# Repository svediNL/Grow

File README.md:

# Grow
This project uses a `Python` program in combination with an `Arduino Mega` to monitor and control factors that are involved with plant growth.

It is supposed to be used as an open-source, modular platform for growers that want to find (or create) optimal growing conditions for the growth of their plants.

The main program is started by running `python gui.py`. 
Through GUI:
- User can choose to enable/diable light as well as control intensity 
    - Manual control
    - Automatic configurable day/night cycle
- Pump is controlled with a PWM setpoint (0-255) and has external enable/disable button. 
    - The pump is interlocked (meaning it will stop) when the float switch is open, to prevent overflow or keep water at a certain level.
- Moisture value and temperature values are logged
  - Current values displayed seperatly

On the microcontroller, the following devices can be configured:
- X amount of `moisture sensor`s [Analog Input, Digital Output] 
- X amount of h-brigde `pump`s [2x PWM Outout]
- X amount of water level `float switch`es [Digital Input]
- X amount of `valve relay`s [Digital Output]
- X amount of `NTC thermistor`s [Analog Input]
- X amount of RGBW-channel `LED driver`s [PWM Output]
- Light dimming door switch [Digital Input]

## /Grow
Software suite for plant environment control.

## /Grow/app
Application directory for main application. 

### /Grow/app/config.py
Configuration of the grow setup. 
Device can be defined here and must be in accordance with the configuration installed on the arduino slave (grow.h)

### /Grow/app/gui.py
Main program.

Run in terminal using: `~/Grow/app$ python gui.py`

Dependencies: `matplotlib`, `tkinter`

### /Grow/app/comms.py
Custom library for communication with arduino.

Dependencies: `pySerial`

## /Grow/arduino

### /Grow/arduino/grow.h
Devices are defined here.

## Installing python modules
### matplotlib
`pip install matpotlib`

### pySerial
`pip install pyserial`
``

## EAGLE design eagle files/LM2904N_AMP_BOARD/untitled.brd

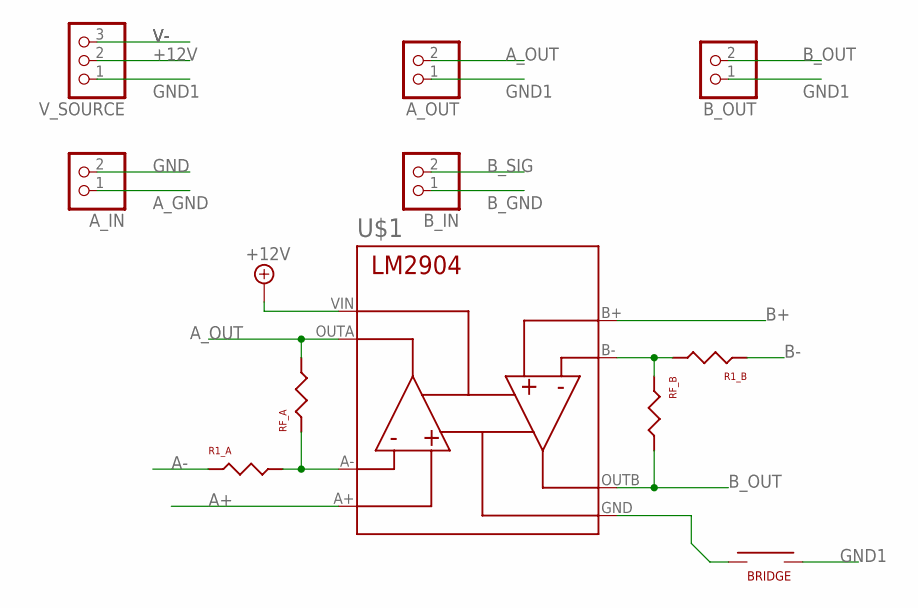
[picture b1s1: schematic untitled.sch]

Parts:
A_IN: PINHD-1X2; 1X02
A_OUT: PINHD-1X2; 1X02
B_IN: PINHD-1X2; 1X02
B_OUT: PINHD-1X2; 1X02
R1_A, R1_B: RESISTOR
RF_A: RESISTOR
RF_B: RESISTOR
U$1: LM2904
U$2: BRIDGE
V_SOURCE: PINHD-1X3; 1X03

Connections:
+12V: U$1.VIN, V_SOURCE.2
A+: U$1.A+
A-: R1_A.P$1
A_GND: A_IN.1
A_OUT: A_OUT.2, RF_A.P$2, U$1.OUTA
B+: U$1.B+
B-: R1_B.P$1
B_GND: B_IN.1
B_OUT: B_OUT.2, RF_B.P$2, U$1.OUTB
B_SIG: B_IN.2
GND: A_IN.2
GND1: A_OUT.1, B_OUT.1, U$2.P$2, V_SOURCE.1
unnamed: R1_B.P$2, RF_B.P$1, U$1.B-
unnamed: R1_A.P$2, RF_A.P$1, U$1.A-
V-: U$1.GND, U$2.P$1, V_SOURCE.3

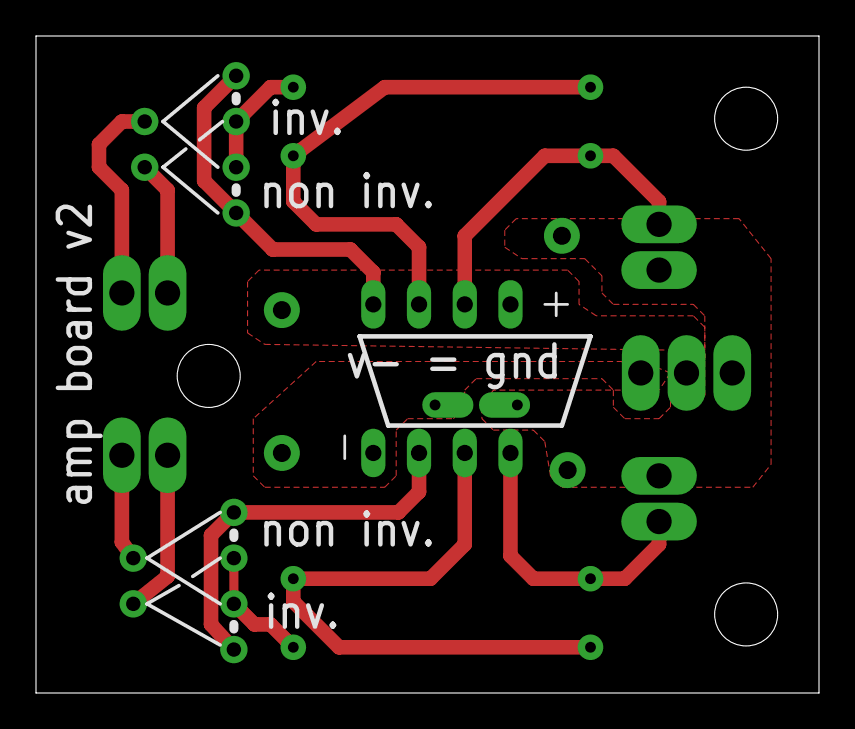
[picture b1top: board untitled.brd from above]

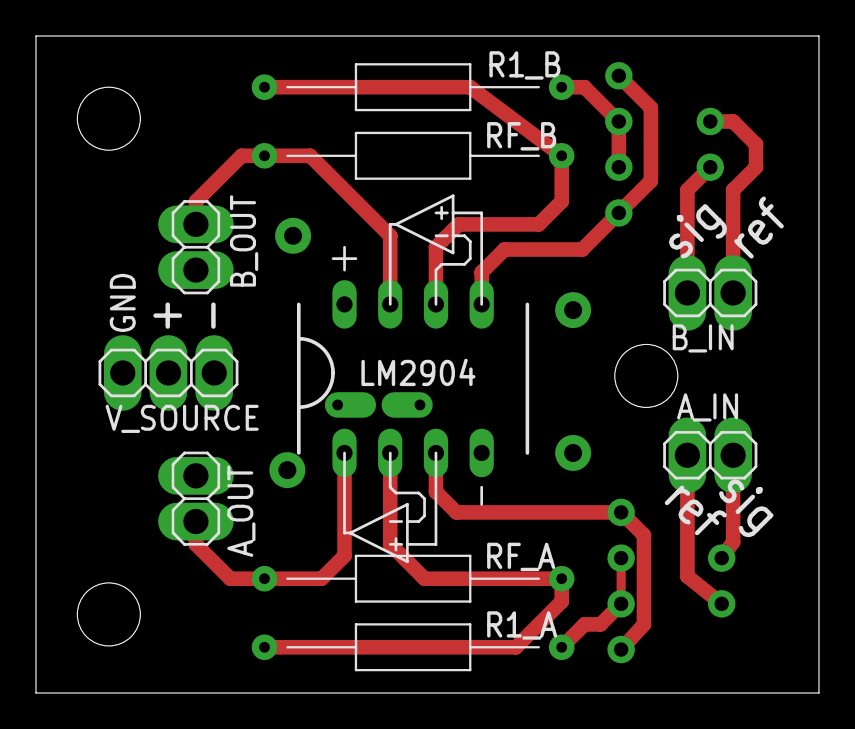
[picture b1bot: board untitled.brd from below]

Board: 2 copper layers, 43.5 x 36.5 mm, 11 parts (6 on the bottom side), 7 nets.

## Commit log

2019-10-13 Initial
2019-10-14 prettyfication
    print commands they way they are sent
2019-11-16 pull from raspberry
2019-11-16 serial interface
    can now manually send commands
2019-12-14 Update gui.py
    Did a lot of changes on structure of packing widget
    Added program part to tkinter
    PRogram now updates current day time
2019-12-14 Daytime nighttime
    Added daytime controller
2019-12-14 version 1.0
    disable printing of arduino during init
    fully implemented daylight simulator
2019-12-14 Update comms.py
    oops unsaved changes
    - disable waiting for io list printing to finish
2019-12-15 update v1.1
    Added read/write to serial interface
    Added live status frame
    Configurable animation time
2019-12-15 Update gui.py
    small fix to autoscaling of plot (visually better)
    disable signal generator
2019-12-15 better comm
    Better communication end of message/ack using "@"
2019-12-15 Removed old project
2019-12-15 added relay to gui
    added relay
    commenting
2019-12-15 v1.2
2019-12-22 v1.3
    - display input/output text with prepended </> in terminal
    - plot lamp output and pump output together with moisture level & light output
    - Added GET_PUMP & GET_LAMP command to arduino
    - Had to change default command state of -1 to enum NO_COMMAND
2019-12-28 Multiple variable plotting
    Made thermocouple variable array type -> added index parameter to get_temp()
    Added setting of relay output (fans) when setting light output
2019-12-28 v1.4
2019-12-29 Array-ification
    Added more arrays so setup is more modular/scalable
2019-12-29 Moar array
2020-01-05 v1.5
    - Tested valve sytem using relays
    - More arrays and use of configuration document
2020-01-14 Fixes
    Fixed daylight sequence
    Plot TOD instead of minutes ago
    Fix to get lamp command when door is open
2020-01-20 v1.6
    - Added door switch to lower light levels when door is opened
    - Fixed daylight mode after messing it up
2020-01-25 seperate plotting tabs
2020-02-06 Window scaling
    Window scaling & improvement to debug mode
2020-02-08 Fix to daylight
    Missing parametter
2020-02-23 sttuff
2020-02-23 GUI enhancements
2020-02-23 more
2020-02-24 v 2.0
    mayor gui improvement
2020-04-05 Added pandas dependency
    pandas for logging
2020-04-05 use functions to get global variable
2020-04-05 use function to set globals
2020-04-05 print 4 testing
2020-04-13 visuals
2020-05-22 Configure multiple float switches
    TODO interlock linking
2020-05-24 Checkbox/radiobutton color
2020-05-30 added drop down list of com ports
2020-06-16 second timer sketch
2020-06-20 mostly working timekeeping
2020-06-20 Tested & calculation works now
    to do test on different configurations
    & extend functions for implementationin grow
2020-06-21 Timer seems pretty stable added modulus compensation for remaining drift
2020-06-21 Include standard arduin definition files
2020-06-28 Update timekeeping
    in one week 10s time difference
2020-06-28 Implemented tomeleeping into arduino main
2020-06-28 python 3 ran on macos
2020-06-28 Added clock commands to serial
2020-07-25 for testing subtimers
    Added subtimers for future scheduled pumping etc on slave
2020-07-25 Update comms.h
    forgot to save
2020-07-26 made subtimers part of TimeKeeper (masterClock)
2020-07-26 Restructure
    Made Grow-class so functions cane implemented to link devices (for timer to pump lijnking)
2020-07-26 so much stuff in grow that arduino_main is now almost empty
2020-07-26 Update gui.py
    Right bar is now live status + a notebook for device control (so serial & direct contro are merged) to allow for more features on one page
2020-07-28 implemented scheduler in arduino side
    Although not yet on serial comm
2020-08-21 arduino implementation of scheduler
2020-08-25 Added schematic etc for amplification board
2020-08-25 And the board ;)
2020-09-08 arduino code fixes
    - doucle definitions in actuators.cpp/.h
    - configure one channel (white) on output because the others were using the wrong timer
2020-09-15 Plotting rework
    Do plotting without notebook & use only a single animate() thread
2020-09-20 quick push
2020-09-20 Fixes from the field
2020-09-20 good fixes
2020-09-21 GUI looks good again
2020-10-24 Scheduling table
    TODO send command / interpret settings
2021-02-24 test commit using pi4 teminal git
2021-03-08 Update timekeeping.cpp
    disable printing of time (debugging)
2021-03-08 Add AM2315 I2C sensor
    AM2315_TEMP() -> get temperature
    AM2315_HUM() -> get humidity
    using adafruit AM2315 library
2021-03-08 Update gui.py
    add am2315 to plotting
2021-03-14 Plotting is now properly implemented
    Before the variables were 'static' now trhey are defined by the config.py document, so now all the variables are plotted/logged
2024-11-02 Add option to switch between dark / light theme
2024-11-02 Fixes after problems with tkinter
    Had to upgrade python from 3.6 to 3.11 (tkinter from v8.5 to v8.6) due to compatibility issues with OS. Oops...
    Change calling order of tk objects + added more printing
2024-11-02 Add font definition(s)
    Split system configuration and gui configuration
2024-11-08 Add heading fonts
